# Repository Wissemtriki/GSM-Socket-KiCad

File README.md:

# GSM Socket KiCad

This project presents the **PCB design of a GSM socket** using **KiCad**.  
It includes the complete KiCad project files, schematics, and PCB layout, suitable for GSM module integration in embedded systems and IoT devices.

### Tools Used
- KiCad EDA
- GSM Socket Module

### Project Contents
- KiCad project folder (.pro, .sch, .kicad_pcb, etc.)
- PCB layout files
- Schematic files

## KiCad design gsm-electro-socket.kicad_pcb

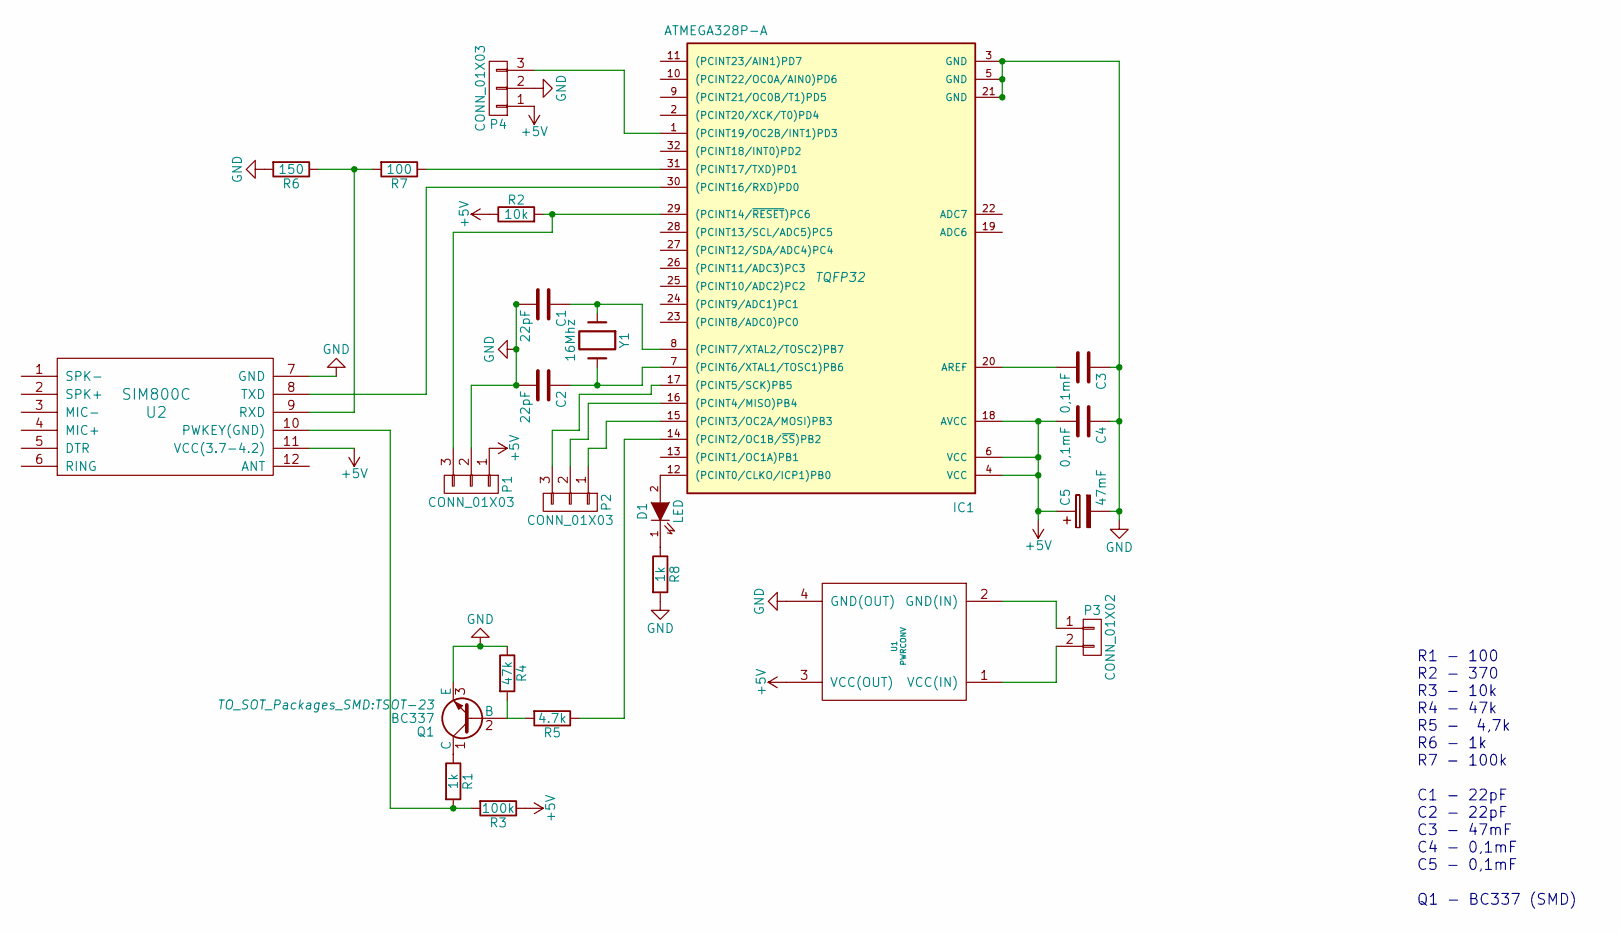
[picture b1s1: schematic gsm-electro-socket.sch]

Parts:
C1, C2: 22pF; C_0805_HandSoldering
C3, C4: 0,1mF; C_0805_HandSoldering
C5: 47mF; CP_Elec_8x10.5
D1: LED; LED_D2.0mm_W4.0mm_H2.8mm_FlatTop
IC1: ATMEGA328P-A; TQFP32
P1, P2, P4: CONN_01X03; Pin_Header_Angled_1x03_Pitch2.54mm
P3: CONN_01X02; Pin_Header_Angled_1x02_Pitch2.54mm
Q1: BC337; TSOT-23
R1, R8: 1k; R_0805_HandSoldering
R2: 10k; R_0805_HandSoldering
R3: 100k; R_0805_HandSoldering
R4: 47k; R_0805_HandSoldering
R5: 4.7k; R_0805_HandSoldering
R6: 150; R_0805_HandSoldering
R7: 100; R_0805_HandSoldering
U1: PWRCONV; PwrConvStepDown
U2: SIM800C; sim800c
Y1: 16Mhz; Crystal_SMD_HC49-SD_HandSoldering

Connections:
+5V: C4.2, C5.1, IC1.4 (VCC), IC1.6 (VCC), IC1.18 (AVCC), P1.1, P4.1, R2.1, R3.1, U1.3 (VCC(OUT)), U2.11 (VCC(3.7-4.2))
GND: C1.2, C2.2, C3.1, C4.1, C5.2, IC1.3 (GND), IC1.5 (GND), IC1.21 (GND), P1.2, P4.2, Q1.3 (E), R4.1, R6.2, R8.2, U1.4 (GND(OUT)), U2.7 (GND)
unnamed: C1.1, IC1.8 ((PCINT7/XTAL2/TOSC2)PB7), Y1.1
unnamed: C2.1, IC1.7 ((PCINT6/XTAL1/TOSC1)PB6), Y1.2
unnamed: C3.2, IC1.20 (AREF)
unnamed: D1.1 (K), R8.1
unnamed: D1.2 (A), IC1.12 ((PCINT0/CLKO/ICP1)PB0)
unnamed: IC1.1 ((PCINT19/OC2B/INT1)PD3), P4.3
unnamed: IC1.14 ((PCINT2/OC1B/~SS~)PB2), R5.1
unnamed: IC1.15 ((PCINT3/OC2A/MOSI)PB3), P2.1
unnamed: IC1.16 ((PCINT4/MISO)PB4), P2.2
unnamed: IC1.17 ((PCINT5/SCK)PB5), P2.3
unnamed: IC1.29 ((PCINT14/~RESET~)PC6), P1.3, R2.2
unnamed: IC1.30 ((PCINT16/RXD)PD0), U2.8 (TXD)
unnamed: IC1.31 ((PCINT17/TXD)PD1), R7.1
unnamed: P3.1, U1.2 (GND(IN))
unnamed: P3.2, U1.1 (VCC(IN))
unnamed: Q1.1 (C), R1.1
unnamed: Q1.2 (B), R4.2, R5.2
unnamed: R1.2, R3.2, U2.10 (PWKEY(GND))
unnamed: R6.1, R7.2, U2.9 (RXD)

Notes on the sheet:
R1 - 100 R2 - 370 R3 - 10k R4 - 47k R5 - 4,7k R6 - 1k R7 - 100k C1 - 22pF C2 - 22pF C3 - 47mF C4 - 0,1mF C5 - 0,1mF Q1 - BC337 (SMD)

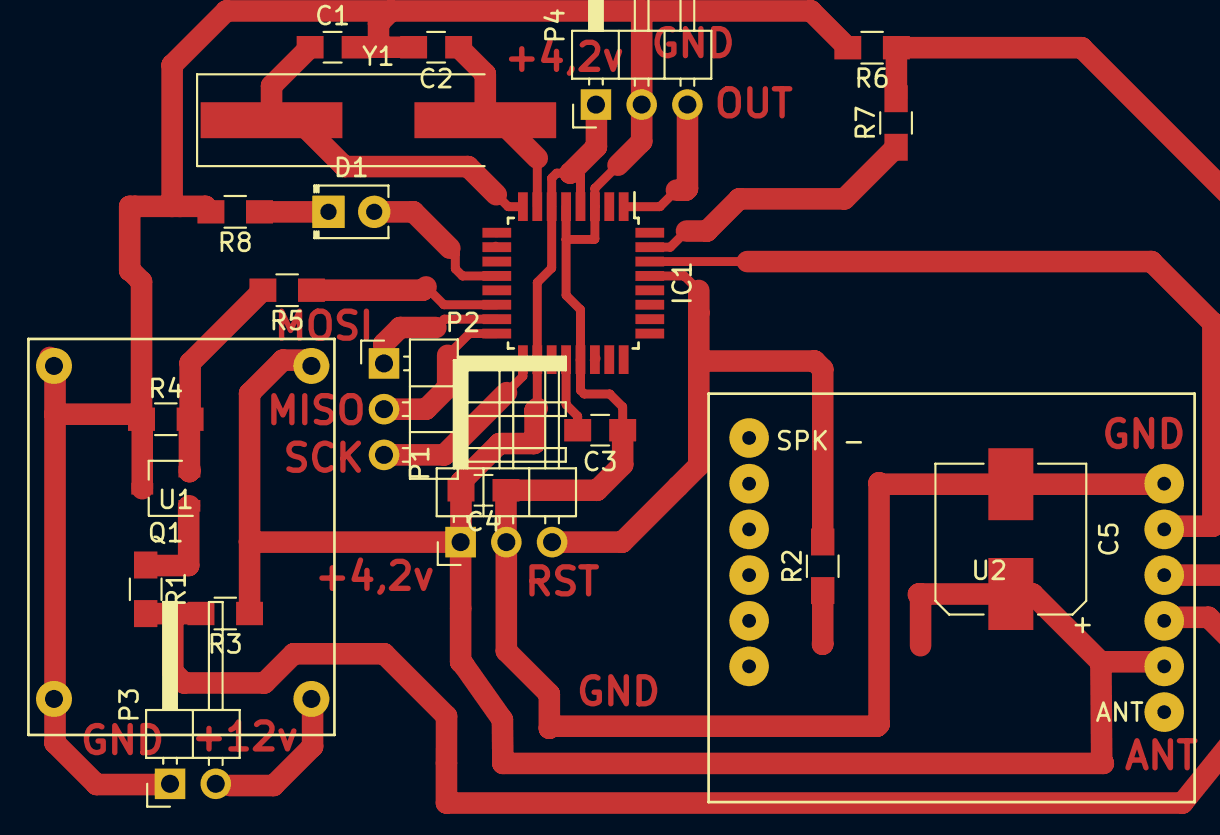
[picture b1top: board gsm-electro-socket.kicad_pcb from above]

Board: 2 copper layers, 23 parts (0 on the bottom side), 21 nets.

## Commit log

2025-11-13 Initial commit - GSM socket PCB design using KiCad
2025-11-13 Add README.md with project overview
